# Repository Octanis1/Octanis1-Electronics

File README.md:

This repo contains all Octanis 1 electronics schematics, BOM, etc.

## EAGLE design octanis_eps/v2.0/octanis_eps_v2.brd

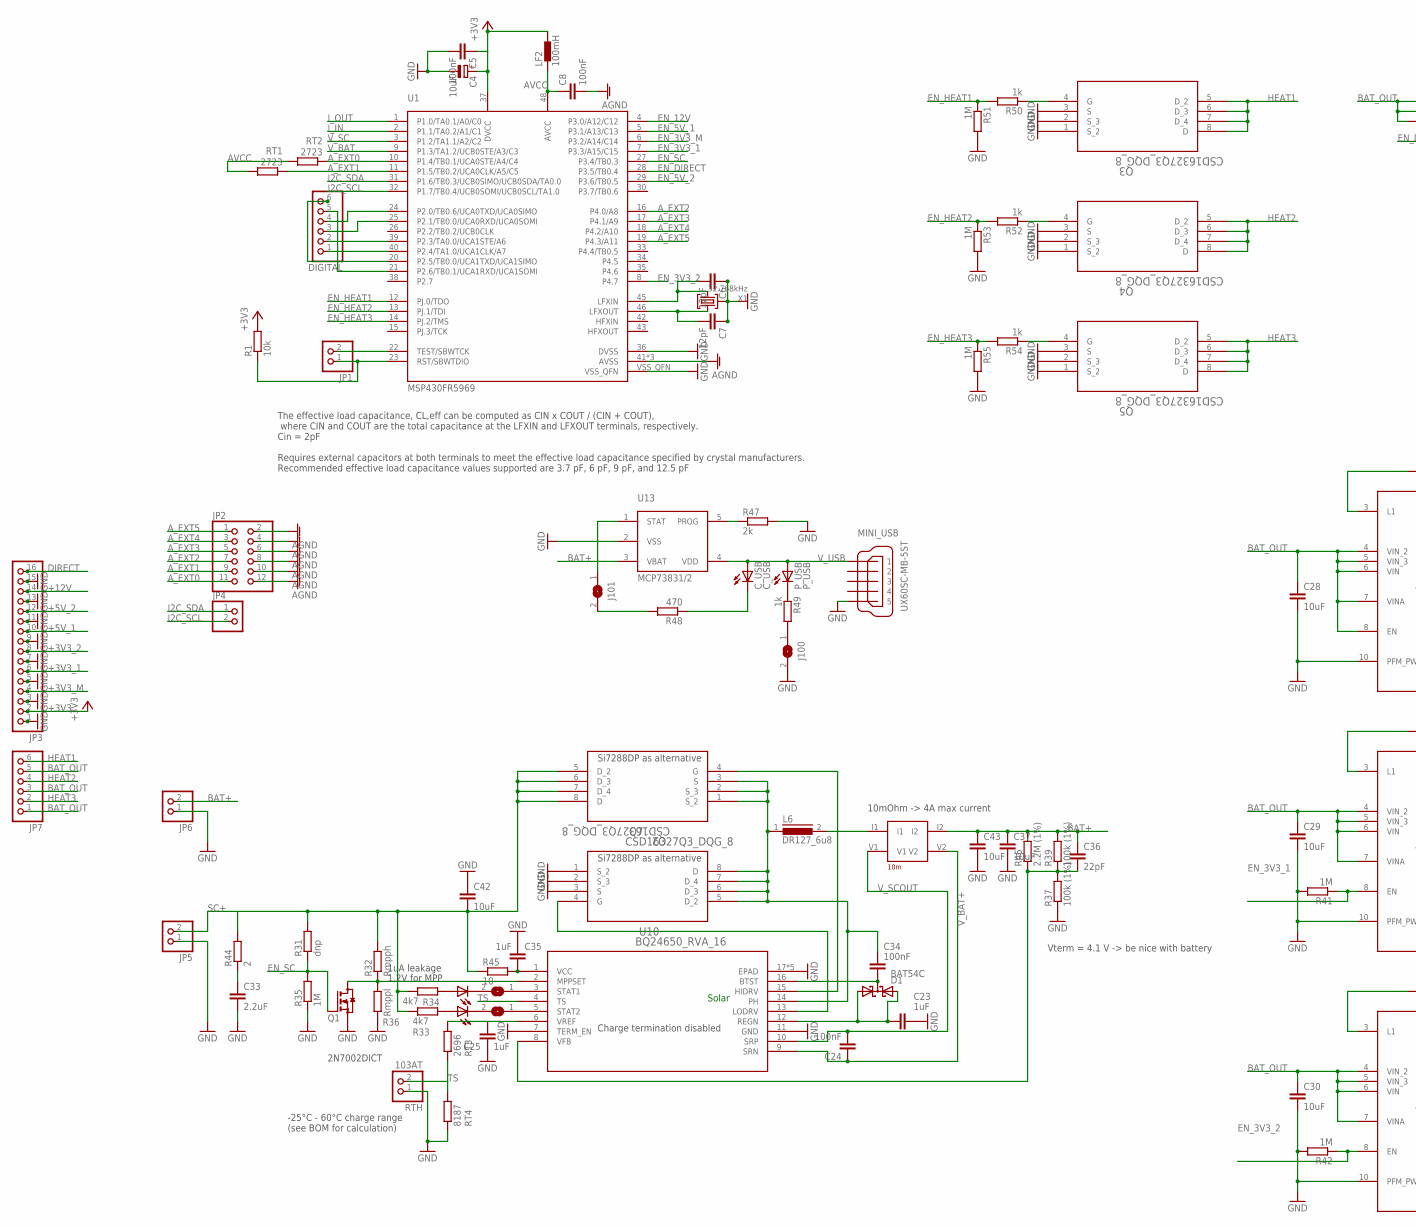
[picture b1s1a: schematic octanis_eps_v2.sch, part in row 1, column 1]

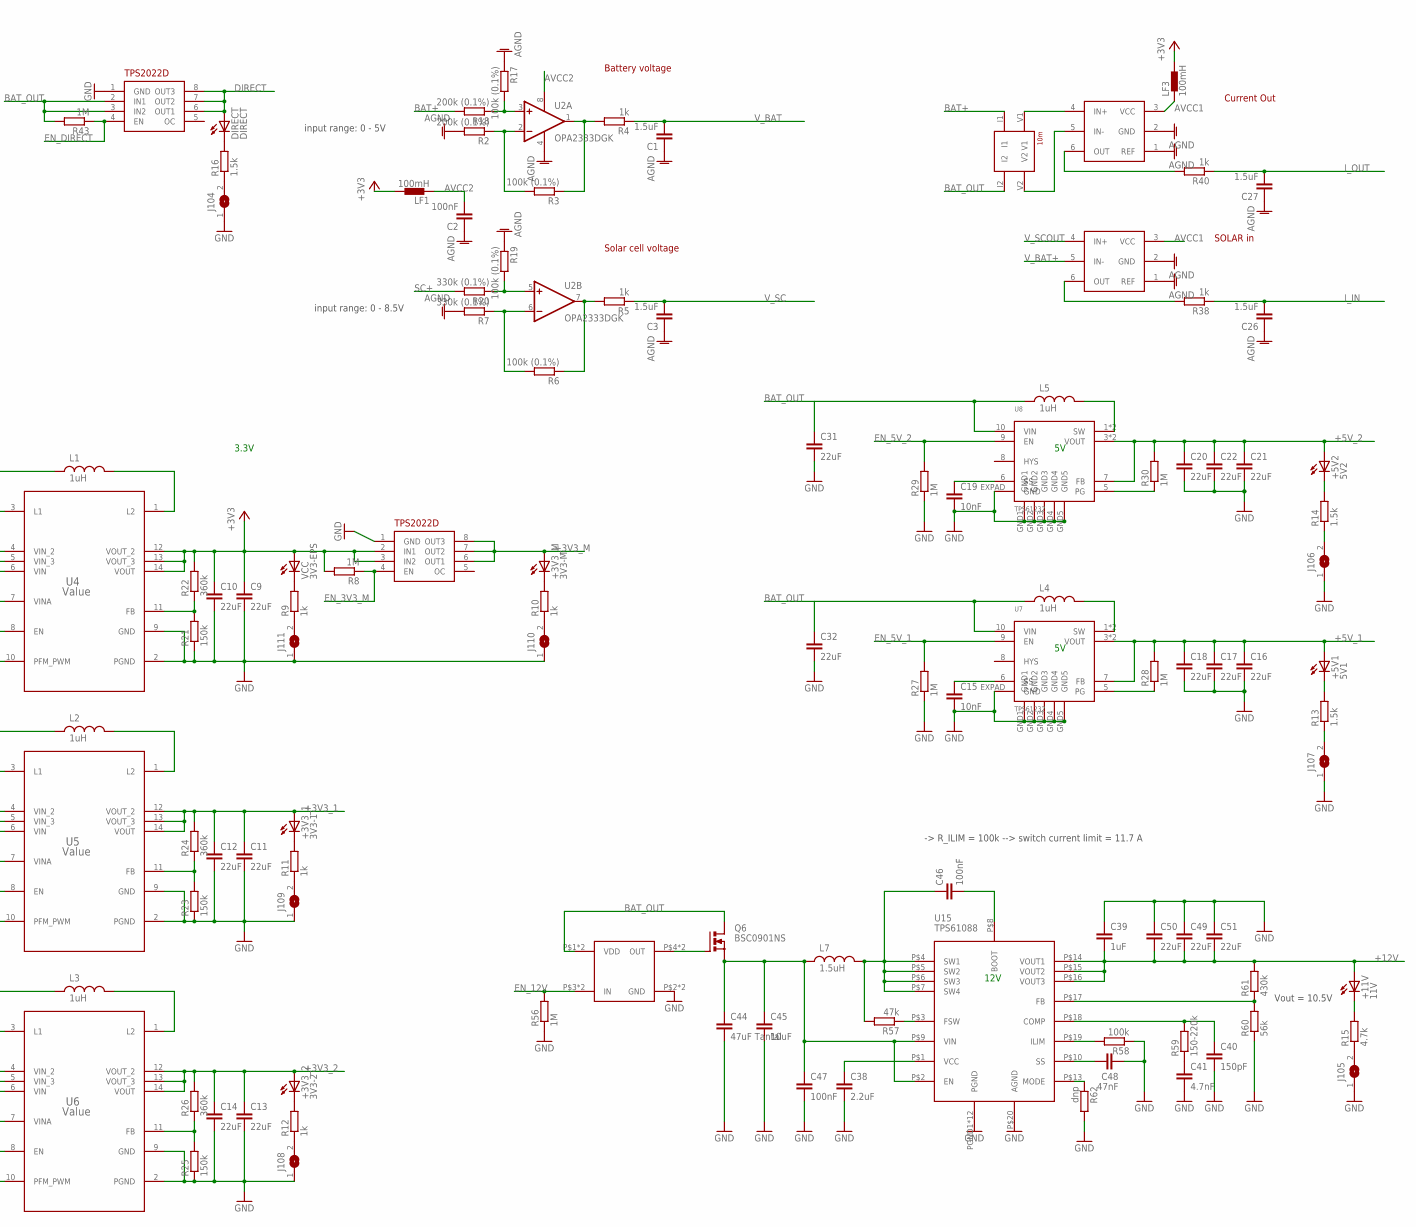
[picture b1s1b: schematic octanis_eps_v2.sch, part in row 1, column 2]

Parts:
+3V3_1: 3V3-1; CHIPLED_0603
+3V3_2: 3V3-2; CHIPLED_0603
+3V3_M: 3V3-M; CHIPLED_0603
+5V1: 5V1; CHIPLED_0603
+5V2: 5V2; CHIPLED_0603
+11V: 11V; CHIPLED_0603
C1, C3, C26, C27: 1.5uF; C0603
C2, C5, C8, C24, C34, C46, C47: 100nF; C0603
C4: 10uF; A/3216-18R
C6, C7: 12pF; C0603
C9, C10, C11, C12, C13, C14, C16, C17, C18, C20, C21, C22, C31, C32, C49, C50, C51: 22uF; C0805
C15, C19: 10nF; C0603
C23, C25, C35, C39: 1uF; C0603
C28, C29, C30, C37, C42, C43, C45: 10uF; C0805
C33, C38: 2.2uF; C0603
C36: 22pF; C0603
C40: 150pF; C0603
C41: 4.7nF; C0603
C44: 47uF Tantal; C1210
C48: 47nF; C0603
C_USB: C_USB; CHIPLED_0603
D1: BAT54C; SOT23
DIGITAL: PINHD-1X6B; 1X06-BIG
DIRECT: DIRECT; CHIPLED_0603
J100, J101, J102, J103, J104, J105, J106, J107, J108, J109, J110, J111: SJ
JP1, JP4, JP5, JP6: PINHD-1X2; 1X02
JP2: PINHD-2X6; 2X06
JP3: PINHD-1X16; 1X16
JP7: PINHD-1X6; 1X06
L1, L2, L3, L4, L5: 1uH; XFL4020
L6: DR127_6u8; DR127
L7: 1.5uH; XFL4020
LF1, LF2, LF3: 100mH; 0402
MINI_USB: UX60SC-MB-5ST
P_USB: P_USB; CHIPLED_0603
Q1: BSS123; SOT23
Q2, Q3, Q4, Q5, Q7: CSD16327Q3_DQG_8; DQG8
Q6: BSC0901NS; PG-TDSON-8
R1: 10k; R0603
R2, R18: 200k (0.1%); R0603
R3, R6, R17, R19: 100k (0.1%); R0603
R4, R5, R9, R10, R11, R12, R38, R40, R49, R50, R52, R54: 1k; R0603
R7, R20: 330k (0.1%); R0603
R8, R27, R28, R29, R30, R35, R41, R42, R43, R51, R53, R55, R56: 1M; R0603
R13, R14, R16: 1.5k; R0603
R15: 4.7k; R0603
R21, R23, R25: 150k; R0603
R22, R24, R26: 360k; R0603
R31, R62: dnp; R0603
R32: Rmpph; R0603
R33, R34: 4k7; R0603
R36: Rmppl; R0603
R37, R39: 100k (1%); R0603
R44: 2; R2010
R45: 10; R1206
R46: 2.2M (1%); R0603
R47: 2k; R0603
R48: 470; R0603
R57: 47k; R0603
R58: 100k; R0603
R59: 150-220k; R0603
R60: 56k; R0603
R61: 430k; R0603
RS1, RS2: 10m; 4PADS_RESISTOR
RT1, RT2: 2723; R0603
RT3: 2696; R0603
RT4: 8187; R0603
RTH: 103AT; 1X02
STAT1, STAT2: 5V-ok; CHIPLED_0603
U1: MSP430FR5969; S-PVQFN-N48
U2: OPA2333DGK; MSOP08
U3, U9: TPS2022D; SO8
U4, U5, U6: Value; RNC0014A
U7, U8: TPS61232; S-PVSON-N10
U10: BQ24650_RVA_16; RVA16_2P14X2P14
U11, U12: INA213; SC70-6
U13: MCP73831/2; SOT23-5
U14: MIC5019; QFN-4
U15: TPS61088; R-PVQFN-N20
VCC: 3V3-EPS; CHIPLED_0603
X1: 32.768kHz; MS3V-T1R

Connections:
+3V3: C4.+, C5.1, C9.1, C10.1, JP3.2, LF1.2, LF2.2, LF3.2, R1.2, R8.2, R22.2, U1.37 (DVCC), U3.2 (IN1), U3.3 (IN2), U4.12 (VOUT_2), U4.13 (VOUT_3), U4.14 (VOUT), VCC.A
+3V3_1: +3V3_1.A, C11.1, C12.1, JP3.6, R24.2, U5.12 (VOUT_2), U5.13 (VOUT_3), U5.14 (VOUT)
+3V3_2: +3V3_2.A, C13.1, C14.1, JP3.8, R26.2, U6.12 (VOUT_2), U6.13 (VOUT_3), U6.14 (VOUT)
+3V3_M: +3V3_M.A, JP3.4, U3.6 (OUT1), U3.7 (OUT2), U3.8 (OUT3)
+5V_1: +5V1.A, C16.1, C17.1, C18.1, JP3.10, R28.2, U7.3 (VOUT), U7.4 (VOUT), U7.7 (FB)
+5V_2: +5V2.A, C20.1, C21.1, C22.1, JP3.12, R30.2, U8.3 (VOUT), U8.4 (VOUT), U8.7 (FB)
+12V: +11V.A, C39.2, C49.2, C50.2, C51.2, JP3.14, R61.2, U15.P$14 (VOUT1), U15.P$15 (VOUT2), U15.P$16 (VOUT3)
AGND: C1.1, C2.1, C3.1, C8.2, C26.1, C27.1, JP2.2, JP2.4, JP2.6, JP2.8, JP2.10, JP2.12, R2.2, R7.2, R17.1, R19.1, U1.41 (AVSS), U1.44 (AVSS), U1.47 (AVSS), U2.4 (V-), U11.1 (REF), U11.2 (GND), U12.1 (REF), U12.2 (GND)
AVCC: C8.1, LF2.1, RT1.1, RT2.1, U1.48 (AVCC)
AVCC1: LF3.1, U11.3 (VCC), U12.3 (VCC)
AVCC2: C2.2, LF1.1, U2.8 (V+)
A_EXT0: JP2.11, RT2.2, U1.10 (P1.4/TB0.1/UCA0STE/A4/C4)
A_EXT1: JP2.9, RT1.2, U1.11 (P1.5/TB0.2/UCA0CLK/A5/C5)
A_EXT2: JP2.7, U1.16 (P4.0/A8)
A_EXT3: JP2.5, U1.17 (P4.1/A9)
A_EXT4: JP2.3, U1.18 (P4.2/A10)
A_EXT5: JP2.1, U1.19 (P4.3/A11)
BAT+: C36.1, C37.1, C43.1, JP6.2, R18.2, R39.2, R46.2, RS1.I1, RS2.I2, U13.3 (VBAT)
BAT_11V: C44.1, C45.1, C47.1, L7.P$1 (1), Q6.1 (S), Q6.2 (S), Q6.3 (S), U15.P$2 (EN), U15.P$9 (VIN)
BAT_OUT: C28.1, C29.1, C30.1, C31.1, C32.1, JP7.1, JP7.3, JP7.5, L4.P$1 (1), L5.P$1 (1), Q6.5 (D), Q6.6 (D), Q6.7 (D), Q6.8 (D), R43.2, RS1.I2, U4.4 (VIN_2), U4.5 (VIN_3), U4.6 (VIN), U4.7 (VINA), U4.8 (EN), U5.4 (VIN_2), U5.5 (VIN_3), U5.6 (VIN), U5.7 (VINA), U6.4 (VIN_2), U6.5 (VIN_3), U6.6 (VIN), U6.7 (VINA), U7.10 (VIN), U8.10 (VIN), U9.2 (IN1), U9.3 (IN2), U14.P1 (VDD), U14.P$1 (VDD)
DIRECT: DIRECT.A, JP3.16, U9.6 (OUT1), U9.7 (OUT2), U9.8 (OUT3)
EN_3V3_1: R41.1, U1.7 (P3.3/A15/C15), U5.8 (EN)
EN_3V3_2: R42.1, U1.8 (P4.7), U6.8 (EN)
EN_3V3_M: R8.1, U1.6 (P3.2/A14/C14), U3.4 (EN)
EN_5V_1: R27.2, U1.5 (P3.1/A13/C13), U7.9 (EN)
EN_5V_2: R29.2, U1.29 (P3.6/TB0.5), U8.9 (EN)
EN_12V: R56.2, U1.4 (P3.0/A12/C12), U14.P3 (IN), U14.P$3 (IN)
EN_DIRECT: R43.1, U1.28 (P3.5/TB0.4), U9.4 (EN)
EN_HEAT1: R50.2, R51.1, U1.12 (PJ.0/TDO)
EN_HEAT2: R52.2, R53.1, U1.13 (PJ.1/TDI)
EN_HEAT3: R54.2, R55.1, U1.14 (PJ.2/TMS)
EN_SC: Q1.1 (G), R31.1, R35.2, U1.27 (P3.4/TB0.3)
GND: C4.-, C5.2, C6.1, C7.1, C9.2, C10.2, C11.2, C12.2, C13.2, C14.2, C15.2, C16.2, C17.2, C18.2, C19.2, C20.2, C21.2, C22.2, C23.2, C25.2, C28.2, C29.2, C30.2, C31.2, C32.2, C33.2, C35.2, C37.2, C38.2, C39.1, C40.2, C41.2, C42.1, C43.2, C44.2, C45.2, C47.2, C48.2, C49.1, C50.1, C51.1, J100.2, J104.1, J105.1, J106.1, J107.1, J108.1, J109.1, J110.1, J111.1, JP3.1, JP3.3, JP3.5, JP3.7, JP3.9, JP3.11, JP3.13, JP3.15, JP5.1, JP6.1, MINI_USB.5, Q1.2 (S), Q3.1 (S_2), Q3.2 (S_3), Q3.3 (S), Q4.1 (S_2), Q4.2 (S_3), Q4.3 (S), Q5.1 (S_2), Q5.2 (S_3), Q5.3 (S), Q7.1 (S_2), Q7.2 (S_3), Q7.3 (S), R21.1, R23.1, R25.1, R27.1, R29.1, R35.1, R36.1, R37.1, R41.2, R42.2, R47.2, R51.2, R53.2, R55.2, R56.1, R58.1, R60.1, R62.2, RT4.2, RTH.1, U1.36 (DVSS), U1.VSS_QFN, U3.1 (GND), U4.2 (PGND), U4.9 (GND), U4.10 (PFM_PWM), U5.2 (PGND), U5.9 (GND), U5.10 (PFM_PWM), U6.2 (PGND), U6.9 (GND), U6.10 (PFM_PWM), U7.EXPAD (GND), U7.GND1, U7.GND2, U7.GND3, U7.GND4, U7.GND5, U8.EXPAD (GND), U8.GND1, U8.GND2, U8.GND3, U8.GND4, U8.GND5, U9.1 (GND), U10.7 (TERM_EN), U10.11 (GND), U10.17 (EPAD), U10.V (EPAD), U10.V_1 (EPAD), U10.V_2 (EPAD), U10.V_3 (EPAD), U13.2 (VSS), U14.P2 (GND), U14.P$2 (GND), U15.P$20 (AGND), U15.PGND1 (PGND), U15.PGND2 (PGND), U15.PGND3 (PGND), U15.PGND4 (PGND), U15.PGND5 (PGND), U15.PGND6 (PGND), U15.PGND7 (PGND), U15.PGND8 (PGND), U15.PGND9 (PGND), U15.PGND10 (PGND), U15.PGND11 (PGND), U15.PGND12 (PGND), X1.P3 (GND)
HEAT1: JP7.6, Q3.5 (D_2), Q3.6 (D_3), Q3.7 (D_4), Q3.8 (D)
HEAT2: JP7.4, Q4.5 (D_2), Q4.6 (D_3), Q4.7 (D_4), Q4.8 (D)
HEAT3: JP7.2, Q5.5 (D_2), Q5.6 (D_3), Q5.7 (D_4), Q5.8 (D)
I2C_SCL: JP4.2, U1.32 (P1.7/TB0.4/UCB0SOMI/UCB0SCL/TA1.0)
I2C_SDA: JP4.1, U1.31 (P1.6/TB0.3/UCB0SIMO/UCB0SDA/TA0.0)
IND: L4.P$2 (2), U7.1 (SW), U7.2 (SW)
IND1: L5.P$2 (2), U8.1 (SW), U8.2 (SW)
I_IN: C26.2, R38.1, U1.2 (P1.1/TA0.2/A1/C1)
I_OUT: C27.2, R40.1, U1.1 (P1.0/TA0.1/A0/C0)
LED1: +5V2.C, R14.2
LED2: DIRECT.C, R16.2
LED5: +5V1.C, R13.2
unnamed: L1.P$1 (1), U4.3 (L1)
unnamed: R28.1, U7.5 (PG)
unnamed: L1.P$2 (2), U4.1 (L2)
unnamed: L6.2, RS2.I1
unnamed: C15.1, U7.6 (SS)
unnamed: L2.P$1 (1), U5.3 (L1)
unnamed: L2.P$2 (2), U5.1 (L2)
unnamed: R62.1, U15.P$13 (MODE)
unnamed: Q6.4 (G), U14.P4 (OUT), U14.P$4 (OUT)
unnamed: L3.P$1 (1), U6.3 (L1)
unnamed: L3.P$2 (2), U6.1 (L2)
unnamed: JP1.1, R1.1, U1.23 (RST/SBWTDIO)
unnamed: J107.2, R13.1
unnamed: JP1.2, U1.22 (TEST/SBWTCK)
unnamed: C7.2, U1.46 (LFXOUT), X1.P1 (1)
unnamed: C6.2, U1.45 (LFXIN), X1.P2 (2)
unnamed: DIGITAL.3, U1.25 (P2.1/TB0.0/UCA0RXD/UCA0SOMI)
unnamed: R3.1, R4.2, U2.1 (OUT)
unnamed: R2.1, R3.2, U2.2 (-IN)
unnamed: R17.2, R18.1, U2.3 (+IN)
unnamed: R5.2, R6.1, U2.7 (OUT)
unnamed: R6.2, R7.1, U2.6 (-IN)
unnamed: R19.2, R20.1, U2.5 (+IN)
unnamed: R40.2, U11.6 (OUT)
unnamed: R38.2, U12.6 (OUT)
unnamed: Q5.4 (G), R54.1
unnamed: DIGITAL.4, U1.24 (P2.0/TB0.6/UCA0TXD/UCA0SIMO)
unnamed: DIGITAL.2, U1.39 (P2.3/TA0.0/UCA1STE/A6)
unnamed: DIGITAL.1, U1.40 (P2.4/TA1.0/UCA1CLK/A7)
unnamed: Q4.4 (G), R52.1
unnamed: RS1.V1, U11.4 (IN+)
unnamed: RS1.V2, U11.5 (IN-)
unnamed: R21.2, R22.1, U4.11 (FB)
unnamed: R23.2, R24.1, U5.11 (FB)
unnamed: DIGITAL.5, U1.21 (P2.6/TB0.1/UCA1RXD/UCA1SOMI)
unnamed: Q3.4 (G), R50.1
unnamed: C46.2, U15.P$8 (BOOT)
unnamed: +3V3_M.C, R10.2
unnamed: J110.2, R10.1
unnamed: DIGITAL.6, U1.20 (P2.5/TB0.0/UCA1TXD/UCA1SIMO)
unnamed: C33.1, R44.1
unnamed: R9.2, VCC.C
unnamed: R30.1, U8.5 (PG)
unnamed: J111.2, R9.1
unnamed: +3V3_2.C, R12.2
unnamed: J108.2, R12.1
unnamed: +11V.C, R15.2
unnamed: J105.2, R15.1
unnamed: C46.1, L7.P$2 (2), R57.2, U15.P$4 (SW1), U15.P$5 (SW2), U15.P$6 (SW3), U15.P$7 (SW4)
unnamed: +3V3_1.C, R11.2
unnamed: J109.2, R11.1
unnamed: R57.1, U15.P$3 (FSW)
unnamed: C41.1, R59.1
unnamed: J106.2, R14.1
unnamed: C48.1, U15.P$10 (SS)
unnamed: R58.2, U15.P$19 (ILIM)
unnamed: C40.1, R59.2, U15.P$18 (COMP)
unnamed: C38.1, U15.P$1 (VCC)
unnamed: R60.2, R61.1, U15.P$17 (FB)
unnamed: C19.1, U8.6 (SS)
unnamed: R25.2, R26.1, U6.11 (FB)
unnamed: R47.1, U13.5 (PROG)
unnamed: Q1.3 (D), R32.1, R36.2, U10.2 (MPPSET)
unnamed: J101.1, U13.1 (STAT)
unnamed: R34.1, STAT2.A
unnamed: J103.2, STAT1.C
unnamed: J102.2, STAT2.C
unnamed: R33.1, STAT1.A
unnamed: J103.1, U10.5 (STAT2)
unnamed: J102.1, U10.3 (STAT1)
unnamed: C25.1, RT3.1, U10.6 (VREF)
unnamed: C35.1, R45.2, U10.1 (VCC)
unnamed: J101.2, R48.2
unnamed: C_USB.C, R48.1
unnamed: C34.1, L6.1, Q2.1 (S_2), Q2.2 (S_3), Q2.3 (S), Q7.5 (D_2), Q7.6 (D_3), Q7.7 (D_4), Q7.8 (D), U10.14 (PH)
unnamed: J104.2, R16.1
unnamed: P_USB.C, R49.1
unnamed: J100.1, R49.2
unnamed: Q2.4 (G), U10.15 (HIDRV)
unnamed: Q7.4 (G), U10.13 (LODRV)
unnamed: C36.2, R37.2, R39.1, R46.1, U10.8 (VFB)
unnamed: C23.1, D1.1 (A1), D1.2 (A2), U10.12 (REGN)
unnamed: C34.2, D1.3 (CC), U10.16 (BTST)
SC+: C42.2, JP5.2, Q2.5 (D_2), Q2.6 (D_3), Q2.7 (D_4), Q2.8 (D), R20.2, R31.2, R32.2, R33.2, R34.2, R44.2, R45.1
TS: RT3.2, RT4.1, RTH.2, U10.4 (TS)
V_BAT: C1.2, R4.1, U1.9 (P1.3/TA1.2/UCB0STE/A3/C3)
V_BAT+: C24.1, RS2.V2, U10.9 (SRN), U12.5 (IN-)
V_SC: C3.2, R5.1, U1.3 (P1.2/TA1.1/A2/C2)
V_SCOUT: C24.2, RS2.V1, U10.10 (SRP), U12.4 (IN+)
V_USB: C_USB.A, MINI_USB.1, P_USB.A, U13.4 (VDD)

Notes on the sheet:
Solar
3.3V
12V
Battery voltage
Solar cell voltage
SOLAR in
Current Out
Vout = 10.5V
1.2V for MPP
1uA leakage
Charge termination disabled
Vterm = 4.1 V -> be nice with battery
10mOhm -> 4A max current
2N7002DICT
Si7288DP as alternative
-> R_ILIM = 100k --> switch current limit = 11.7 A
The effective load capacitance, CL,eff can be computed as CIN x COUT / (CIN + COUT), where CIN and COUT are the total capacitance at the LFXIN and LFXOUT terminals, respectively. Cin = 2pF Requires external capacitors at both terminals to meet the effective load capacitance specified by crystal man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
input range: 0 - 8.5V
input range: 0 - 5V
-25°C - 60°C charge range (see BOM for calculation)

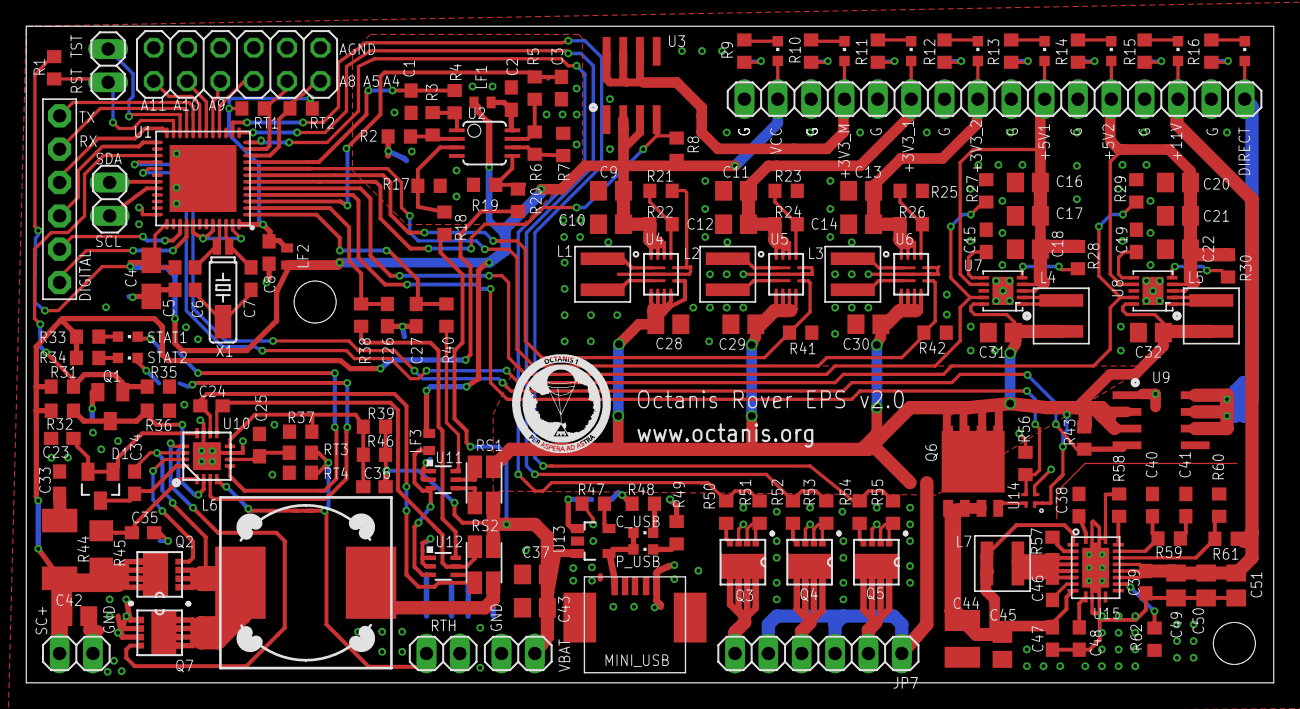
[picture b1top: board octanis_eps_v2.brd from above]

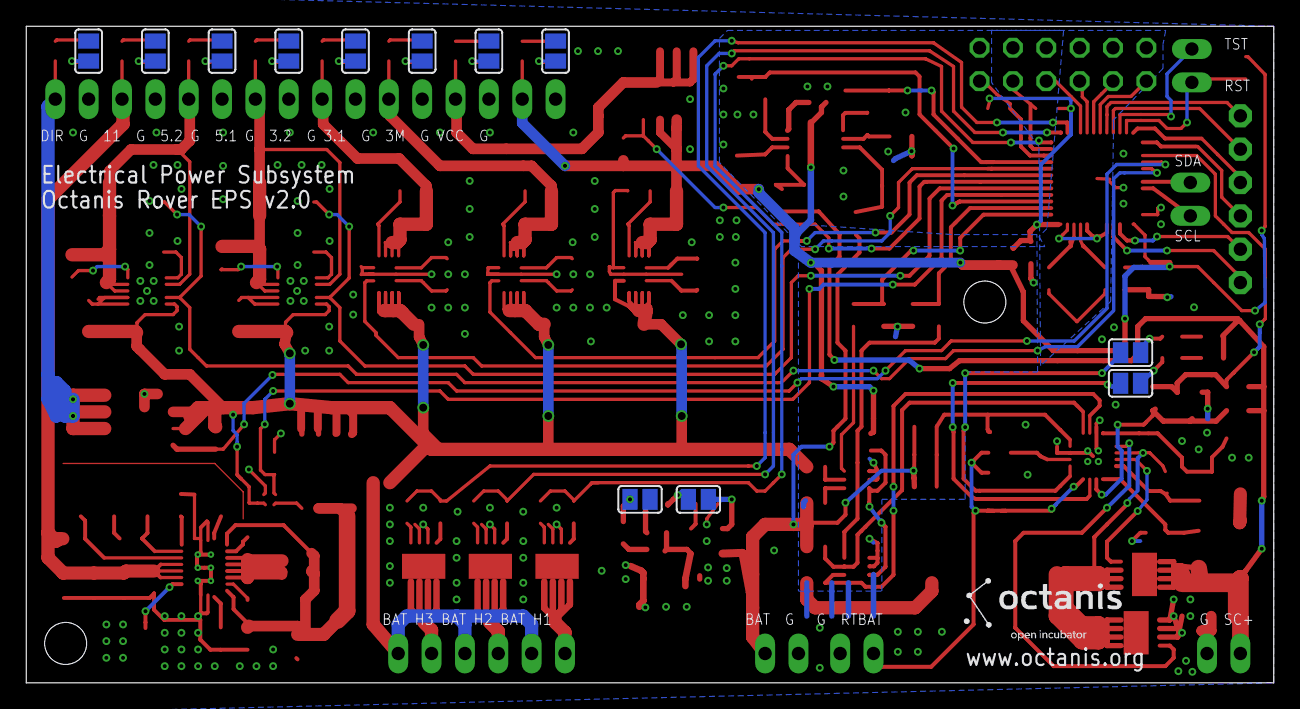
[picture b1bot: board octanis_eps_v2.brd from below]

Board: 2 copper layers, 95.0 x 50.0 mm, 187 parts (12 on the bottom side), 135 nets.

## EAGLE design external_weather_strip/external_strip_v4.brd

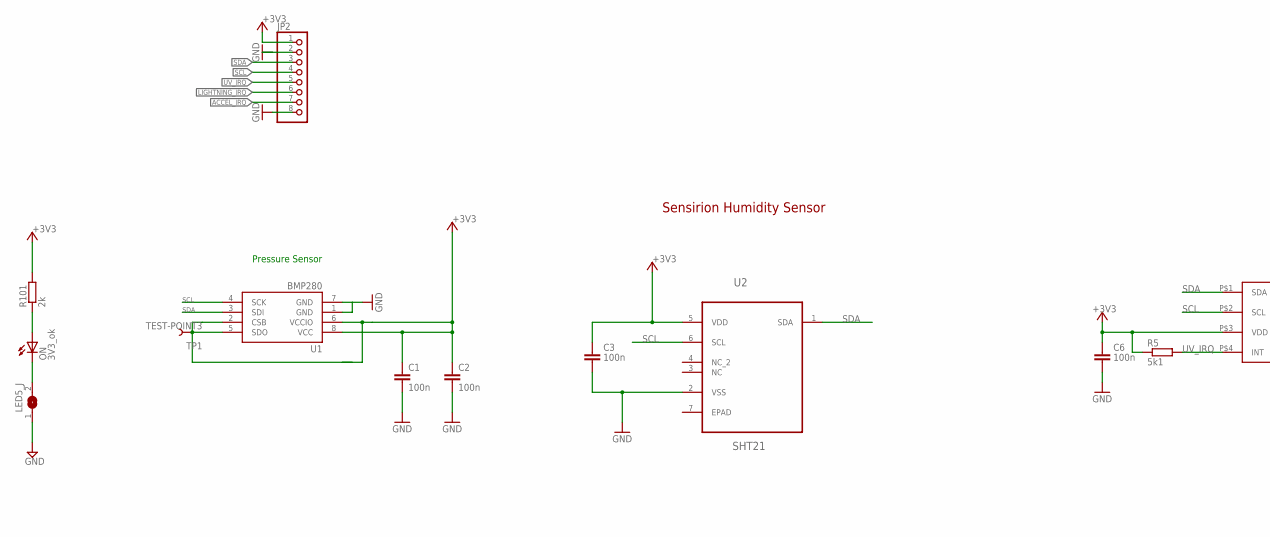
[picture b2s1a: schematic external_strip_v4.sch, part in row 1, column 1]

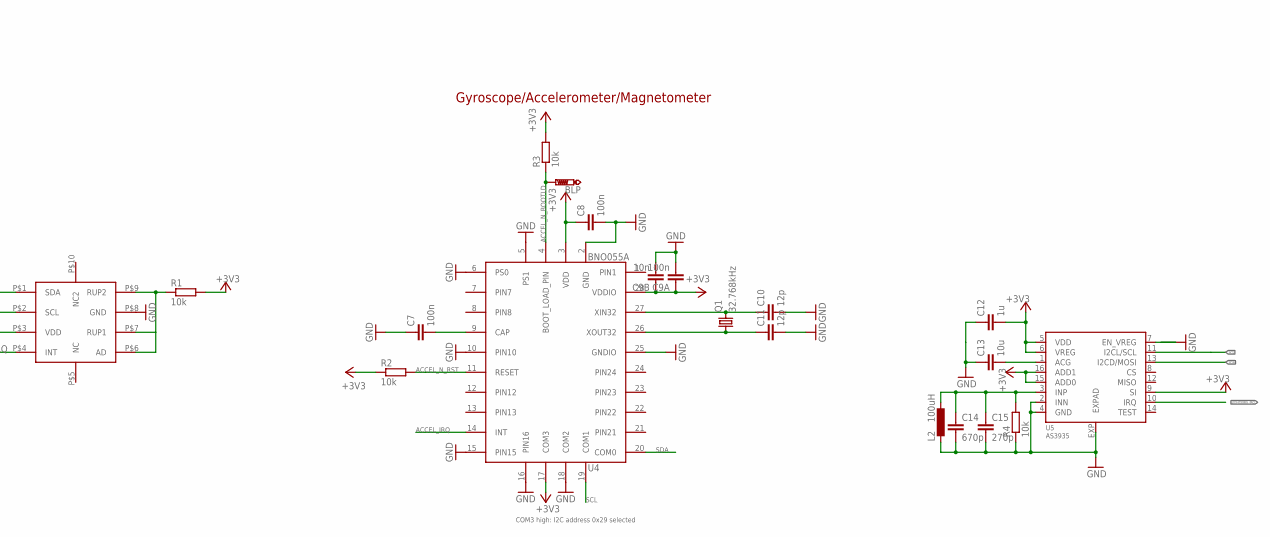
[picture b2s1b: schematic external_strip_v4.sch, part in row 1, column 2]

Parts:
BLP: PTR1B1,27; B1,27
C1, C2, C3, C6, C7, C8, C9A: 100n; C0603
C9B: 10n; C0603
C10, C11: 12p; C0603
C12: 1u; C0603
C13: 10u; C0603
C14: 670p; C0603
C15: 270p; C0603
JP2: PINHD-1X8; 1X08
L2: 100uH; COILCRAFT
LED5_J: SJ
ON: 3V3_ok; CHIPLED_0603
Q1: 32.768kHz; FC-12M
R1, R2, R3, R4: 10k; R0603
R5: 5k1; R0603
R101: 2k; R0603
TP1: TEST-POINT3; PAD.03X.03
U1: BMP280; LGA8
U2: SHT21; DFN300X300X110-7N
U3: SI1133; DFN2X2
U4: BNO055A; BNO055
U5: AS3935; 16LDMLPQ

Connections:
+3V3: C1.1, C2.1, C3.1, C6.1, C8.1, C9A.1, C9B.1, C12.2, JP2.1, R1.2, R2.1, R3.2, R5.1, R101.2, TP1.P$1, U1.2 (CSB), U1.5 (SDO), U1.6 (VCCIO), U1.8 (VCC), U2.5 (VDD), U3.P$3 (VDD), U4.3 (VDD), U4.17 (COM3), U4.28 (VDDIO), U5.5 (VDD), U5.6 (VREG), U5.9 (SI), U5.15 (ADD0), U5.16 (ADD1)
ACCEL_IRQ: JP2.7, U4.14 (INT)
ACCEL_N_BOOTLD: BLP.TP, R3.1, U4.4 (BOOT_LOAD_PIN)
ACCEL_N_RST: R2.2, U4.11 (RESET)
GND: C1.2, C2.2, C3.2, C6.2, C7.1, C8.2, C9A.2, C9B.2, C10.2, C11.2, C12.1, C13.1, C14.2, C15.2, JP2.2, JP2.8, L2.2, LED5_J.1, R4.1, U1.1 (GND), U1.7 (GND), U2.2 (VSS), U3.P$8 (GND), U4.2 (GND), U4.5 (PS1), U4.6 (PS0), U4.10 (PIN10), U4.15 (PIN15), U4.16 (PIN16), U4.18 (COM2), U4.25 (GNDIO), U5.2 (INN), U5.4 (GND), U5.7 (EN_VREG), U5.EXP (EXPAD)
LIGHTNING_IRQ: JP2.6, U5.10 (IRQ)
unnamed: C13.2, U5.1 (ACG)
unnamed: LED5_J.2, ON.C
unnamed: C14.1, C15.1, L2.1, R4.2, U5.3 (INP)
unnamed: ON.A, R101.1
unnamed: R1.1, U3.P$6 (AD), U3.P$7 (RUP1), U3.P$9 (RUP2)
unnamed: C7.2, U4.9 (CAP)
unnamed: C10.1, Q1.2, U4.27 (XIN32)
unnamed: C11.1, Q1.1, U4.26 (XOUT32)
SCL: JP2.4, U1.4 (SCK), U2.6 (SCL), U3.P$2 (SCL), U4.19 (COM1), U5.11 (I2CL/SCL)
SDA: JP2.3, U1.3 (SDI), U2.1 (SDA), U3.P$1 (SDA), U4.20 (COM0), U5.13 (I2CD/MOSI)
UV_IRQ: JP2.5, R5.2, U3.P$4 (INT)

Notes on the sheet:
Sensirion Humidity Sensor
Pressure Sensor
Gyroscope/Accelerometer/Magnetometer
COM3 high: I2C address 0x29 selected

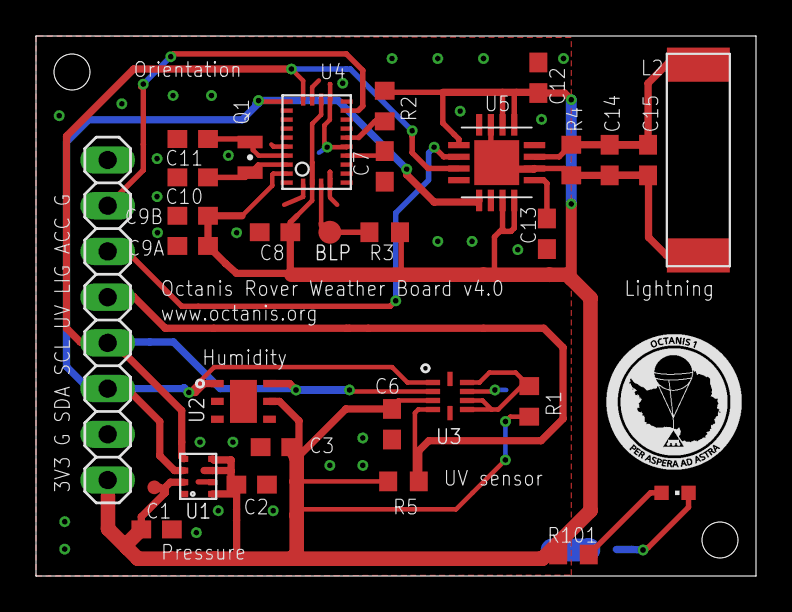
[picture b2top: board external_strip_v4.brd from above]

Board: 2 copper layers, 40.0 x 30.0 mm, 32 parts (1 on the bottom side), 17 nets.

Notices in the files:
parts and their libraries:
SparkFun-Capacitors: Licensing: CC v3.0 Share-Alike You are welcome to use this library for commercial purposes.
SparkFun-Retired: Licensing:Creative Commons ShareAlike 4.0 International - https://creativecommons.org/licenses/by-sa/4.0
